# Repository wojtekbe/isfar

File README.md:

isfar - H-ROV underwater robot
=====

Connectors
==========

I^2C (MICROMATCH-4):
--------
* 1 - SDA
* 2 - SCL
* 3 - GND
* 4 - +3V3

PWR (TBMP/C-GRID-03):
--------
* 1 - +5V
* 2 - GND
* 3 - +12V

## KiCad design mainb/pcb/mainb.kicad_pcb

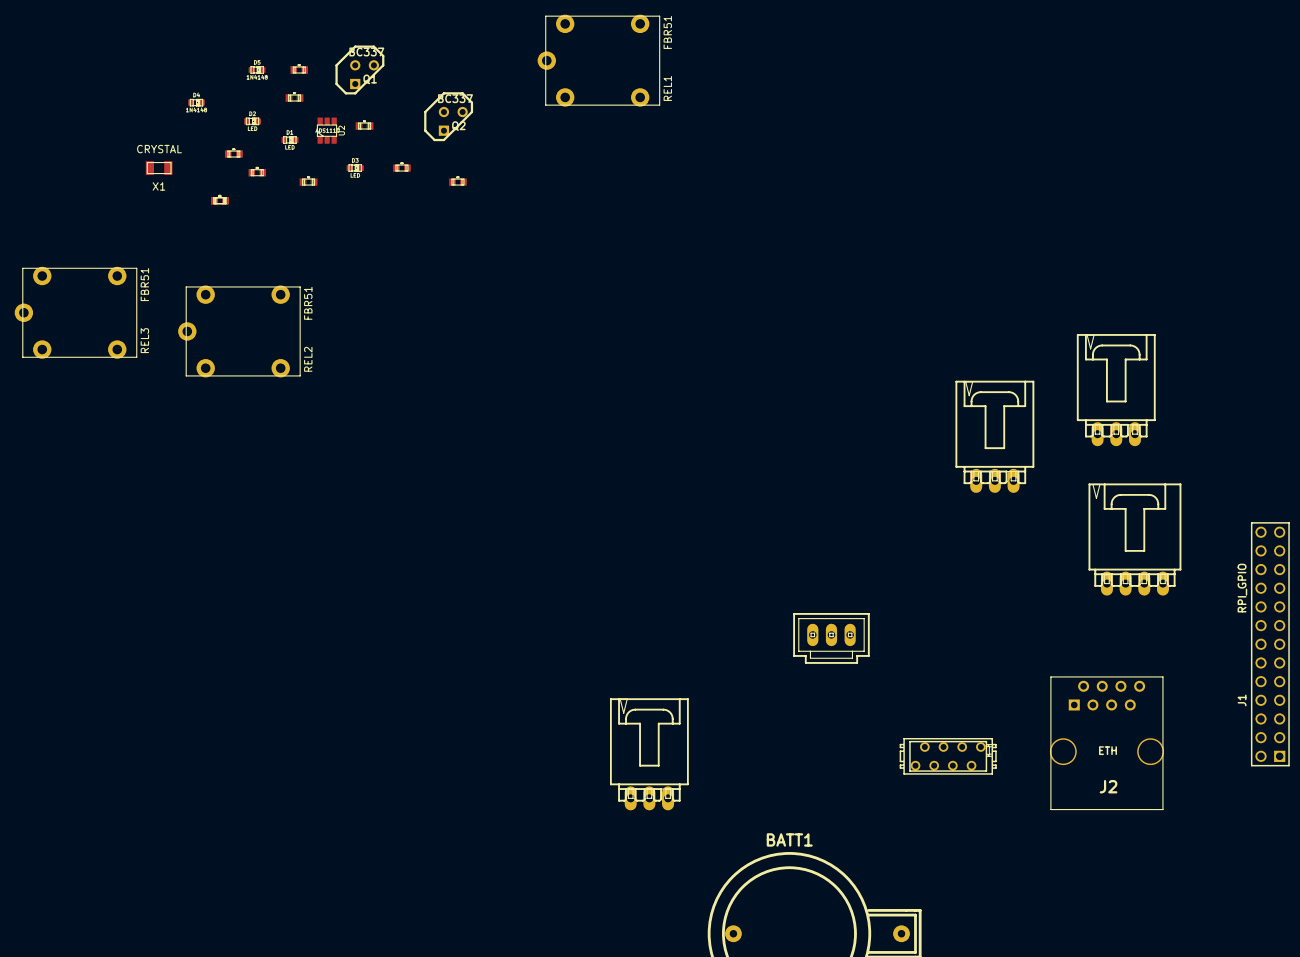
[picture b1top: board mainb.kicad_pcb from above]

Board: 2 copper layers, 31 parts (0 on the bottom side), 27 nets, no tracks yet.

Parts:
BATT1: CR2303; CR2032H
C1, C2: 100n; c_0603
D1, D2, D3: LED; LED-0603
D4, D5: 1N4148; LED-0603
ETH->RPI1: CONN_8; con-amp-micromatch-MICROMATCH-8
J1: RPI_GPIO; pin_array_13x2
J2: ETH; RJ45_8
J3: I2C; WZ04R
J4, J5, J6: I2C; WZ03R
J11: UART; WZ03S
Q1, Q2: BC337; TO92-CBE
R1, R2, R6: ??; c_0603
R4, R5: R; c_0603
R7, R8, R9: 500; c_0603
REL1, REL2, REL3: FBR51
U2: ADS1110; SOT23_6
X1: CRYSTAL; CFPX-217

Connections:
+5C: J3.4, REL1.3
+5V: C1.2, C2.1, D4.2, J1.2, J1.4, R6.1, REL1.1, REL1.2, U2.5
+12V: R1.1, REL2.3
/+3V3: J1.1, R7.2, R8.2, R9.2
/LED1: D1.2, J1.22
/LED2: D2.2, J1.18
/LED3: D3.2, J1.16
/RX: J1.10, J11.2
/RX+: ETH->RPI1.4, J2.3
/RX-: ETH->RPI1.6, J2.6
/TX: J1.8, J11.3
/TX+: ETH->RPI1.1, J2.1
/TX-: ETH->RPI1.3, J2.2
AKU+: REL3.1, REL3.2
unnamed: D5.1, REL2.5
unnamed: D4.1, REL1.5
unnamed: R1.2, R2.1, U2.1
unnamed: D1.1, R9.1
unnamed: D2.1, R8.1
unnamed: D3.1, R7.1
unnamed: D5.2, REL2.1, REL2.2, REL3.3
PoE+: J2.4, J2.5, REL3.5
PoE-: BATT1.2, C1.1, C2.2, J1.6, J1.9, J1.14, J1.20, J1.25, J2.7, J2.8, J3.3, J4.3, J5.3, J6.3, J11.1, R2.2, U2.2, U2.6
REL#1: J1.11, R5.1
REL#2: J1.13, R4.1
SCL: J1.5, J3.2, J4.2, J5.2, J6.2, U2.3
SDA: J1.3, J3.1, J4.1, J5.1, J6.1, U2.4

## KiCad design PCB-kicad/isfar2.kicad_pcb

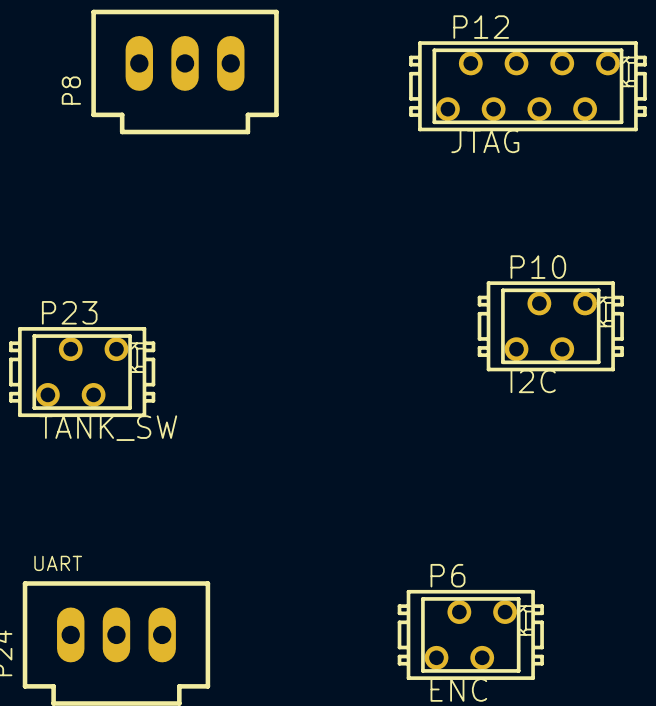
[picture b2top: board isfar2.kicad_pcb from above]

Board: 2 copper layers, 6 parts (0 on the bottom side), 3 nets, no tracks yet.

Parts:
P6: ENC; MICROMATCH-4
P8, P24: UART; 70543-03
P10: I2C; MICROMATCH-4
P12: JTAG; MICROMATCH-8
P23: TANK_SW; MICROMATCH-4

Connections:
+3.3V: P12.2, P23.2, P23.3
+5V: P6.1, P10.4
PoE-: P6.4, P8.1, P10.3, P12.8, P24.1

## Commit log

2013-11-20 libs added, single mainboard (again)
2013-11-20 i2 sidedriver added
2013-11-20 zmieniony ksztalt mainb
2013-11-20 20-11-13 21:08
2013-11-21 21.11.13 23:39
2013-11-22 22.11.13 17:00
2013-11-26 26.11 10:46
2013-11-28 RPi camera board added and library, added servos.lbr
2013-12-03 03-12-13 20:52
2013-12-11 11.12.13 18:50
2013-12-11 11.12.13 18:51
2014-01-26 misc changes
2014-01-28 porzadki w mainb/
2014-01-28 dodano docs/
2014-01-28 rm docs/
2014-01-28 /mainb: 1) pins on relays
2014-01-28 todo file added
2014-01-28 mainb: 3) volt.reg. package dim.
2014-01-28 mainb: 8) leds -> 3V3
2014-01-28 mainb: 7) eth. conn. order
2014-01-28 mainb: 9) battery holder wholes dia
2014-01-28 mainb: 10) RPi UART for debugging
2014-01-28 trinocular/rpicam/ added
2014-02-03 PWM on timer4, and USART2 on Discovery
2014-02-04 sidedriver/readme added
2014-02-04 readmes update
2014-02-04 readmes update ctd...
2014-02-04 fixed USART 0x12 issue
2014-02-10 Signal capturing on TIM3 works
2014-02-11 readme.md modified
2014-02-11 readme.md
2014-02-11 I2C working on Discovery
2014-02-11 rpicam: setup TWI, calibrated servo
2014-02-25 mainb rev. 2 added
2014-02-25 migrating from doscovery to sidedriv. board
2014-02-25 25-02
2014-03-05 trinocular: added app to capture frames from fifo with Opencv
2014-03-08 sidedriver: ledd misc changes
2014-03-11 sidedrv: init funcs for drivers, misc changes
2014-03-11 sidedriver: rm readme.md, pin config in main.c
2014-03-11 rm todo
2014-03-12 sidedriver: i2c improvements in driver-discovery
2014-03-15 sidedriver: improved i2c on discovery
2014-03-15 ignoring *.elf and *.bin
2014-03-15 sidedriver: discovery misc changes
2014-03-15 siderdriver: added i2c support
2014-03-18 some cleanup, ignoring *.o *.hex
2014-03-18 sidedriver: added support for counting encoder ticks, minor improvements
2014-03-19 sidedriver: stopped using STM32F4xx_StdPeriph_Driver, updated Makefile
2014-03-19 sidedriver: misc changes
2014-03-29 siderdriver: initial PID controller implementation
2014-03-29 sidedriver: added support for 2b i2c 'registers'
2014-04-09 sidedriver: PID contr. tests
2014-05-06 sidedriver: some improvements in PID controller
2014-05-07 sidedriver: *.c/*.h split, code cleanup
2014-05-11 sidedriver: PID controller tweaks
2014-05-13 libs/ cleanup
2014-05-13 mainb: mainb_v2 PCB created using kicad
2014-05-13 igoring *-cache.bak
2014-05-14 mainb: mainb_v2 kicad schematic updates
2014-05-14 mainb: kicad sch updates
2014-05-21 sidedriver: fixed a bug in calculating rot. speed (overflow/underflow)
2014-05-28 siderdriver: tankdriver updates, needs some tweaking (transopt.)
2014-05-28 sidedriver: motordriver pid contr. updates
2014-05-28 .gitignore: ignoring kicad_pcb-bak
2014-05-28 some updates in kicad project files, and some cleaning in sidedriver files
2014-05-28 README updates
2014-06-04 sidedriver: resolved transoptor issue
2014-06-07 libs moved somewhere else
2014-06-08 sidedriver: added pinmux.md file
2014-06-08 sidedriver: pinmux.md updateswq
2014-06-08 sidedriver: pinmux.md update
2014-06-08 KiCAD PCB project added
2014-06-08 PCBs: PCB-kicad splitted
2014-06-10 sidedriver: kicad pcb updates
2014-06-10 sidedriver: pid merged to motordriver
2014-06-10 sidedriver: PID tuning
2014-06-10 mainb: added tag for rev1, and provided updates
2014-06-10 sidedriver: Eagle pcb files ranamed
2014-08-05 .gitignore
2014-08-13 sidedriver: added ADC in external port
2014-08-13 sidedriver: pinmux.md updates
2014-08-13 sidedriver: PCB todo file added
2014-08-19 siderdriver: added miliseconds measurement
2014-08-19 sidedriver: ADC calibrated to use with scale
2014-10-07 rpicam: rev2 PCB added
2014-10-21 ledd: added some TODO comments to ledd1.sch
2014-11-03 sidedriver: PCB rev.2 created
2014-11-03 sidedriver: PCB rev.2 updates
2014-12-12 rpicam: updated firmware to work with new PCB
2014-12-16 sidedriver: motordriver for rev.2
2014-12-16 siderdriver: tankdriver for rev.2 in progress...
2015-03-15 rpicam: a script for finding chessboard corners added
2015-04-08 sidedriver: 'make r' doesn't reset the board (compatible with stlink 79b413)
2015-04-08 sidedriver: fix compilation error in tankdriver.c
2015-04-14 sidedriver: warnings, white spaces etc.
2015-04-21 readme update, rst migration
2015-05-19 sidedriver: transopt. -> TIM9_CH2 (not tested)
2015-06-16 sidedriver: tankdriver transoptor to TIM9 work in progress
2015-06-23 sidedriver: debug LED on PA12 support
2015-06-23 sidedriver: toggling debug LED with LEDT()
2015-06-23 sidedriver: tankdriver, isr on TIM9 (transoptor)
2015-07-07 sidedriver: tank resetting procedure
2015-07-17 mainb: initial motor control (mctrl) and tank control (tctrl) scripts
2015-08-11 sidedriver: removed all debug prints
2015-08-11 mainb: scripts moved to proper dir
2015-10-13 sidedriver: turning on tankdriver by default
2015-10-13 mainb: update control scripts
2015-10-29 mainb: adds control client/server scripts
2015-11-03 mainb: ctrl_client: gamepad support
2015-12-03 sidedriver: add delay in td_reset(), change driving speed (PWM)
2015-12-10 sidedriver: tankdriver: td_reset() fix
2015-12-12 sidedriver: tankdriver: MIN/MAX logic
2015-12-12 sidedriver: tankdriver: tank speed set to 75/100
2015-12-12 sidedriver: doscovery: red LED turns on when in HardFault
2015-12-13 sidedriver: discovery: printf() is now from tinyprintf
2015-12-17 mainb: scripts: video server (raspivid+nc) and client (nc+mplayer)
2016-01-26 mainb: updated ctrl scripts, hflipped the video
2016-03-09 mainb: script for switching dhcp to client mode
2016-03-12 sidedriver: printf() bug: debug() uses tinyprintf
2016-03-13 siderdriver: all registers to regs.h
2016-03-13 siderdriver: PID: setting Kp, Ki, Kd via I2C
2016-03-15 sidedriver: PID deadzone
2016-03-17 sidedriver: PID: default Kp = 2/10
2016-07-08 trinocular: rpicam hw revisions in single files
2016-07-08 trinocular: dir reorganized
2016-07-08 trinocular: PCB rev.3 - wip
2016-07-21 trinocular: PCB v3 - wip
2016-08-11 trinocular: rpicam_v3 + gerbers
2017-01-20 README.rst added
2017-01-27 rpicam: avr: code reformat, Timer1 support (LEDs)
2017-04-28 readme: Add board images
